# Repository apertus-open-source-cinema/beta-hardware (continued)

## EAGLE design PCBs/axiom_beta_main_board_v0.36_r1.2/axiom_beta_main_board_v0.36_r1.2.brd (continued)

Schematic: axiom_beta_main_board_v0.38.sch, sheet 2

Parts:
ZED1: µZ-FCI-NOHOLES-R; µZ-NOHOLES-R

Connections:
BANK13_00_N: ZED1.89 (_N); also elsewhere on the board
BANK13_00_P: ZED1.87 (_P); also elsewhere on the board
BANK13_01_N: ZED1.90 (_N); also elsewhere on the board
BANK13_01_P: ZED1.88 (_P); also elsewhere on the board
BANK13_02_N: ZED1.93 (_N); also elsewhere on the board
BANK13_02_P: ZED1.91 (_P); also elsewhere on the board
BANK13_03_N: ZED1.94 (_N); also elsewhere on the board
BANK13_03_P: ZED1.92 (_P); also elsewhere on the board
BANK13_04_N: ZED1.195 (_N); also elsewhere on the board
BANK13_04_P: ZED1.193 (_P); also elsewhere on the board
BANK13_05_N: ZED1.196 (_N); also elsewhere on the board
BANK13_05_P: ZED1.194 (_P); also elsewhere on the board
BANK13_06_N: ZED1.199 (_N); also elsewhere on the board
BANK13_06_P: ZED1.197 (_P); also elsewhere on the board
JX1_00_N: ZED1.13 (_N); also elsewhere on the board
JX1_00_P: ZED1.11 (_P); also elsewhere on the board
JX1_01_N: ZED1.14 (_N); also elsewhere on the board
JX1_01_P: ZED1.12 (_P); also elsewhere on the board
JX1_02_N: ZED1.19 (_N); also elsewhere on the board
JX1_02_P: ZED1.17 (_P); also elsewhere on the board
JX1_03_N: ZED1.20 (_N); also elsewhere on the board
JX1_03_P: ZED1.18 (_P); also elsewhere on the board
JX1_04_N: ZED1.25 (_N); also elsewhere on the board
JX1_04_P: ZED1.23 (_P); also elsewhere on the board
JX1_05_N: ZED1.26 (_N); also elsewhere on the board
JX1_05_P: ZED1.24 (_P); also elsewhere on the board
JX1_06_N: ZED1.31 (_N); also elsewhere on the board
JX1_06_P: ZED1.29 (_P); also elsewhere on the board
JX1_07_N: ZED1.32 (_N); also elsewhere on the board
JX1_07_P: ZED1.30 (_P); also elsewhere on the board
JX1_08_N: ZED1.37 (_N); also elsewhere on the board
JX1_08_P: ZED1.35 (_P); also elsewhere on the board
JX1_09_N: ZED1.38 (_N); also elsewhere on the board
JX1_09_P: ZED1.36 (_P); also elsewhere on the board
JX1_10_N: ZED1.43 (_N); also elsewhere on the board
JX1_10_P: ZED1.41 (_P); also elsewhere on the board
JX1_11_N: ZED1.44 (_N); also elsewhere on the board
JX1_11_P: ZED1.42 (_P); also elsewhere on the board
JX1_12_N: ZED1.49 (_N); also elsewhere on the board
JX1_12_P: ZED1.47 (_P); also elsewhere on the board
JX1_13_N: ZED1.50 (_N); also elsewhere on the board
JX1_13_P: ZED1.48 (_P); also elsewhere on the board
JX1_14_N: ZED1.55 (_N); also elsewhere on the board
JX1_14_P: ZED1.53 (_P); also elsewhere on the board
JX1_15_N: ZED1.56 (_N); also elsewhere on the board
JX1_15_P: ZED1.54 (_P); also elsewhere on the board
JX1_16_N: ZED1.63 (_N); also elsewhere on the board
JX1_16_P: ZED1.61 (_P); also elsewhere on the board
JX1_17_N: ZED1.64 (_N); also elsewhere on the board
JX1_17_P: ZED1.62 (_P); also elsewhere on the board
JX1_18_N: ZED1.69 (_N); also elsewhere on the board
JX1_18_P: ZED1.67 (_P); also elsewhere on the board
JX1_19_N: ZED1.70 (_N); also elsewhere on the board
JX1_19_P: ZED1.68 (_P); also elsewhere on the board
JX1_20_N: ZED1.75 (_N); also elsewhere on the board
JX1_20_P: ZED1.73 (_P); also elsewhere on the board
JX1_21_N: ZED1.76 (_N); also elsewhere on the board
JX1_21_P: ZED1.74 (_P); also elsewhere on the board
JX1_22_N: ZED1.83 (_N); also elsewhere on the board
JX1_22_P: ZED1.81 (_P); also elsewhere on the board
JX1_23_N: ZED1.84 (_N); also elsewhere on the board
JX1_23_P: ZED1.82 (_P); also elsewhere on the board
JX2_00_N: ZED1.119 (_N); also elsewhere on the board
JX2_00_P: ZED1.117 (_P); also elsewhere on the board
JX2_01_N: ZED1.120 (_N); also elsewhere on the board
JX2_01_P: ZED1.118 (_P); also elsewhere on the board
JX2_02_N: ZED1.125 (_N); also elsewhere on the board
JX2_02_P: ZED1.123 (_P); also elsewhere on the board
JX2_03_N: ZED1.126 (_N); also elsewhere on the board
JX2_03_P: ZED1.124 (_P); also elsewhere on the board
JX2_04_N: ZED1.131 (_N); also elsewhere on the board
JX2_04_P: ZED1.129 (_P); also elsewhere on the board
JX2_05_N: ZED1.132 (_N); also elsewhere on the board
JX2_05_P: ZED1.130 (_P); also elsewhere on the board
JX2_06_N: ZED1.137 (_N); also elsewhere on the board
JX2_06_P: ZED1.135 (_P); also elsewhere on the board
JX2_07_N: ZED1.138 (_N); also elsewhere on the board
JX2_07_P: ZED1.136 (_P); also elsewhere on the board
JX2_08_N: ZED1.143 (_N); also elsewhere on the board
JX2_08_P: ZED1.141 (_P); also elsewhere on the board
JX2_09_N: ZED1.144 (_N); also elsewhere on the board
JX2_09_P: ZED1.142 (_P); also elsewhere on the board
JX2_10_N: ZED1.149 (_N); also elsewhere on the board
JX2_10_P: ZED1.147 (_P); also elsewhere on the board
JX2_11_N: ZED1.150 (_N); also elsewhere on the board
JX2_11_P: ZED1.148 (_P); also elsewhere on the board
JX2_12_N: ZED1.155 (_N); also elsewhere on the board
JX2_12_P: ZED1.153 (_P); also elsewhere on the board
JX2_13_N: ZED1.156 (_N); also elsewhere on the board
JX2_13_P: ZED1.154 (_P); also elsewhere on the board
JX2_14_N: ZED1.163 (_N); also elsewhere on the board
JX2_14_P: ZED1.161 (_P); also elsewhere on the board
JX2_15_N: ZED1.164 (_N); also elsewhere on the board
JX2_15_P: ZED1.162 (_P); also elsewhere on the board
JX2_16_N: ZED1.169 (_N); also elsewhere on the board
JX2_16_P: ZED1.167 (_P); also elsewhere on the board
JX2_17_N: ZED1.170 (_N); also elsewhere on the board
JX2_17_P: ZED1.168 (_P); also elsewhere on the board
JX2_18_N: ZED1.175 (_N); also elsewhere on the board
JX2_18_P: ZED1.173 (_P); also elsewhere on the board
JX2_19_N: ZED1.176 (_N); also elsewhere on the board
JX2_19_P: ZED1.174 (_P); also elsewhere on the board
JX2_20_N: ZED1.183 (_N); also elsewhere on the board
JX2_20_P: ZED1.181 (_P); also elsewhere on the board
JX2_21_N: ZED1.184 (_N); also elsewhere on the board
JX2_21_P: ZED1.182 (_P); also elsewhere on the board
JX2_22_N: ZED1.189 (_N); also elsewhere on the board
JX2_22_P: ZED1.187 (_P); also elsewhere on the board
JX2_23_N: ZED1.190 (_N); also elsewhere on the board
JX2_23_P: ZED1.188 (_P); also elsewhere on the board

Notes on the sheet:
AXIOM Beta Main Board
Copyright (C) 2014-2020 H.Poetzl Licensed under CERN OHL v.1.2
ZYNQ LVDS Interface

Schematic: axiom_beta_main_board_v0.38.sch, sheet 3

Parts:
X-EAST: FX10-100/10S; FX10A-100S/10
X-WEST: FX10-100/10S; FX10A-100S/10

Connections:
!E_RESET!: X-EAST.19; also elsewhere on the board
!W_RESET!: X-WEST.19; also elsewhere on the board
E_EN: X-EAST.14; also elsewhere on the board
E_I2C_EN: X-EAST.13; also elsewhere on the board
E_I2C_V: X-EAST.11; also elsewhere on the board
E_SCK: X-EAST.12; also elsewhere on the board
E_SCL: X-EAST.15; also elsewhere on the board
E_SDA: X-EAST.17; also elsewhere on the board
E_SDI: X-EAST.16; also elsewhere on the board
E_SDO: X-EAST.18; also elsewhere on the board
E_SPI_V: X-EAST.21; also elsewhere on the board
E_VE_CV: X-EAST.90; also elsewhere on the board
E_VE_OV: X-EAST.93; also elsewhere on the board
E_VE_UV: X-EAST.91; also elsewhere on the board
GND: X-EAST.5, X-EAST.20, X-EAST.23, X-EAST.26, X-EAST.29, X-EAST.31, X-EAST.32, X-EAST.37, X-EAST.38, X-EAST.43, X-EAST.44, X-EAST.49, X-EAST.50, X-EAST.51, X-EAST.52, X-EAST.57, X-EAST.58, X-EAST.63, X-EAST.64, X-EAST.69, X-EAST.70, X-EAST.71, X-EAST.76, X-EAST.77, X-EAST.82, X-EAST.G1, X-EAST.G2, X-EAST.G3, X-EAST.G4, X-EAST.G5, X-EAST.G6, X-EAST.G7, X-EAST.G8, X-EAST.G9, X-EAST.G10, X-WEST.5, X-WEST.20, X-WEST.23, X-WEST.26, X-WEST.29, X-WEST.31, X-WEST.32, X-WEST.37, X-WEST.38, X-WEST.43, X-WEST.44, X-WEST.49, X-WEST.50, X-WEST.51, X-WEST.52, X-WEST.57, X-WEST.58, X-WEST.63, X-WEST.64, X-WEST.69, X-WEST.70, X-WEST.71, X-WEST.76, X-WEST.77, X-WEST.82, X-WEST.G1, X-WEST.G2, X-WEST.G3, X-WEST.G4, X-WEST.G5, X-WEST.G6, X-WEST.G7, X-WEST.G8, X-WEST.G9, X-WEST.G10; also elsewhere on the board
JTAG_V: X-WEST.21; also elsewhere on the board
JX1_00_N: X-EAST.27; also elsewhere on the board
JX1_00_P: X-EAST.25; also elsewhere on the board
JX1_02_N: X-EAST.24; also elsewhere on the board
JX1_02_P: X-EAST.22; also elsewhere on the board
JX1_04_N: X-EAST.30; also elsewhere on the board
JX1_04_P: X-EAST.28; also elsewhere on the board
JX1_06_N: X-EAST.36; also elsewhere on the board
JX1_06_P: X-EAST.34; also elsewhere on the board
JX1_07_N: X-EAST.35; also elsewhere on the board
JX1_07_P: X-EAST.33; also elsewhere on the board
JX1_08_N: X-EAST.42; also elsewhere on the board
JX1_08_P: X-EAST.40; also elsewhere on the board
JX1_09_N: X-EAST.41; also elsewhere on the board
JX1_09_P: X-EAST.39; also elsewhere on the board
JX1_10_N: X-EAST.48; also elsewhere on the board
JX1_10_P: X-EAST.46; also elsewhere on the board
JX1_11_N: X-EAST.47; also elsewhere on the board
JX1_11_P: X-EAST.45; also elsewhere on the board
JX1_12_N: X-WEST.56; also elsewhere on the board
JX1_12_P: X-WEST.54; also elsewhere on the board
JX1_13_N: X-WEST.55; also elsewhere on the board
JX1_13_P: X-WEST.53; also elsewhere on the board
JX1_14_N: X-WEST.62; also elsewhere on the board
JX1_14_P: X-WEST.60; also elsewhere on the board
JX1_15_N: X-WEST.61; also elsewhere on the board
JX1_15_P: X-WEST.59; also elsewhere on the board
JX1_16_N: X-WEST.68; also elsewhere on the board
JX1_16_P: X-WEST.66; also elsewhere on the board
JX1_17_N: X-WEST.67; also elsewhere on the board
JX1_17_P: X-WEST.65; also elsewhere on the board
JX1_18_N: X-WEST.74; also elsewhere on the board
JX1_18_P: X-WEST.72; also elsewhere on the board
JX1_20_N: X-WEST.80; also elsewhere on the board
JX1_20_P: X-WEST.78; also elsewhere on the board
JX1_22_N: X-WEST.75; also elsewhere on the board
JX1_22_P: X-WEST.73; also elsewhere on the board
JX2_01_N: X-EAST.73; also elsewhere on the board
JX2_01_P: X-EAST.75; also elsewhere on the board
JX2_03_N: X-EAST.78; also elsewhere on the board
JX2_03_P: X-EAST.80; also elsewhere on the board
JX2_05_N: X-EAST.72; also elsewhere on the board
JX2_05_P: X-EAST.74; also elsewhere on the board
JX2_06_N: X-EAST.65; also elsewhere on the board
JX2_06_P: X-EAST.67; also elsewhere on the board
JX2_07_N: X-EAST.66; also elsewhere on the board
JX2_07_P: X-EAST.68; also elsewhere on the board
JX2_08_N: X-EAST.59; also elsewhere on the board
JX2_08_P: X-EAST.61; also elsewhere on the board
JX2_09_N: X-EAST.60; also elsewhere on the board
JX2_09_P: X-EAST.62; also elsewhere on the board
JX2_10_N: X-EAST.53; also elsewhere on the board
JX2_10_P: X-EAST.55; also elsewhere on the board
JX2_11_N: X-EAST.54; also elsewhere on the board
JX2_11_P: X-EAST.56; also elsewhere on the board
JX2_12_N: X-WEST.45; also elsewhere on the board
JX2_12_P: X-WEST.47; also elsewhere on the board
JX2_13_N: X-WEST.46; also elsewhere on the board
JX2_13_P: X-WEST.48; also elsewhere on the board
JX2_14_N: X-WEST.39; also elsewhere on the board
JX2_14_P: X-WEST.41; also elsewhere on the board
JX2_15_N: X-WEST.40; also elsewhere on the board
JX2_15_P: X-WEST.42; also elsewhere on the board
JX2_16_N: X-WEST.33; also elsewhere on the board
JX2_16_P: X-WEST.35; also elsewhere on the board
JX2_17_N: X-WEST.34; also elsewhere on the board
JX2_17_P: X-WEST.36; also elsewhere on the board
JX2_19_N: X-WEST.28; also elsewhere on the board
JX2_19_P: X-WEST.30; also elsewhere on the board
JX2_21_N: X-WEST.22; also elsewhere on the board
JX2_21_P: X-WEST.24; also elsewhere on the board
JX2_23_N: X-WEST.25; also elsewhere on the board
JX2_23_P: X-WEST.27; also elsewhere on the board
N_CHK_EN: X-WEST.94
N_CHK_V: X-WEST.92; also elsewhere on the board
N_I2C_EN: X-EAST.7; also elsewhere on the board
N_I2C_V: X-EAST.9; also elsewhere on the board
N_SCK: X-EAST.2; also elsewhere on the board
N_SCL: X-EAST.1; also elsewhere on the board
N_SDA: X-EAST.3; also elsewhere on the board
N_SDI: X-EAST.6; also elsewhere on the board
N_SDO: X-EAST.4; also elsewhere on the board
N_SPI_EN: X-EAST.8; also elsewhere on the board
N_SPI_V: X-EAST.10; also elsewhere on the board
N_VE_CV: X-WEST.96; also elsewhere on the board
N_VE_OV: X-WEST.95; also elsewhere on the board
N_VE_RS: X-WEST.88; also elsewhere on the board
N_VE_UV: X-WEST.85; also elsewhere on the board
N_VN_CV: X-WEST.98; also elsewhere on the board
N_VN_OV: X-WEST.97; also elsewhere on the board
N_VN_RS: X-WEST.86; also elsewhere on the board
N_VN_UV: X-WEST.87; also elsewhere on the board
N_VW_CV: X-WEST.100; also elsewhere on the board
N_VW_OV: X-WEST.99; also elsewhere on the board
N_VW_RS: X-WEST.84; also elsewhere on the board
N_VW_UV: X-WEST.89; also elsewhere on the board
RES1: X-WEST.79
RES2: X-WEST.81
RES3: X-WEST.83
RES4: X-EAST.79
RES5: X-EAST.81
RES6: X-EAST.83
S_CHK_EN: X-EAST.94
S_CHK_V: X-EAST.92; also elsewhere on the board
S_I2C_EN: X-WEST.7; also elsewhere on the board
S_I2C_V: X-WEST.9; also elsewhere on the board
S_SCK: X-WEST.2; also elsewhere on the board
S_SCL: X-WEST.1; also elsewhere on the board
S_SDA: X-WEST.3; also elsewhere on the board
S_SDI: X-WEST.6; also elsewhere on the board
S_SDO: X-WEST.4; also elsewhere on the board
S_SPI_EN: X-WEST.8; also elsewhere on the board
S_SPI_V: X-WEST.10; also elsewhere on the board
S_VE_CV: X-EAST.100; also elsewhere on the board
S_VE_OV: X-EAST.99; also elsewhere on the board
S_VE_RS: X-EAST.84; also elsewhere on the board
S_VE_UV: X-EAST.89; also elsewhere on the board
S_VS_CV: X-EAST.98; also elsewhere on the board
S_VS_OV: X-EAST.97; also elsewhere on the board
S_VS_RS: X-EAST.86; also elsewhere on the board
S_VS_UV: X-EAST.87; also elsewhere on the board
S_VW_CV: X-EAST.96; also elsewhere on the board
S_VW_OV: X-EAST.95; also elsewhere on the board
S_VW_RS: X-EAST.88; also elsewhere on the board
S_VW_UV: X-EAST.85; also elsewhere on the board
TCK: X-WEST.12; also elsewhere on the board
TDI: X-WEST.16; also elsewhere on the board
TDO: X-WEST.18; also elsewhere on the board
TMS: X-WEST.14; also elsewhere on the board
W_I2C_EN: X-WEST.13; also elsewhere on the board
W_I2C_V: X-WEST.11; also elsewhere on the board
W_SCL: X-WEST.15; also elsewhere on the board
W_SDA: X-WEST.17; also elsewhere on the board
W_VW_CV: X-WEST.90; also elsewhere on the board
W_VW_OV: X-WEST.93; also elsewhere on the board
W_VW_UV: X-WEST.91; also elsewhere on the board

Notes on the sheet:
AXIOM Beta Main Board
Copyright (C) 2014-2020 H.Poetzl Licensed under CERN OHL v.1.2
Interface Board Connection

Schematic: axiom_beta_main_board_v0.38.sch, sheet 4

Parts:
C1, C1', C3, C3', C5, C5', C7, C7': C0805-A; 0805-A
C2, C2', C4, C4', C6, C6', C8, C8': C0603-A; 0603-A
PAD1, PAD2, PAD3, PAD4, PAD5, PAD6, PAD7, PAD8, PAD9, PAD10, PAD11, PAD12, PAD13, PAD14, PAD15, PAD16: PINPAD1.27MM; 1.2/0.6
PB-NW: DF12(XX)-20DP-0.5V
PB-SE: DF12(XX)-20DP-0.5V
PCIE-NORTH: PCIE-36-AXIOM-NOPEG; PCIE-36-NOPEG
PCIE-SOUTH: PCIE-36-AXIOM-NOPEG; PCIE-36-NOPEG
PWR-NE: PINHD-2X02_2.54; 2X02
PWR-NW: PINHD-2X02_2.54; 2X02
PWR-SE: PINHD-2X02_2.54; 2X02
PWR-SW: PINHD-2X02_2.54; 2X02
R1, R2, R3, R4, R5, R6: 4k7; 0402-B
U1: PCA9540BDP; SOP65P490X300-8N

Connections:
A_!RST: PB-NW.2; also elsewhere on the board
A_SCL: PB-NW.1; also elsewhere on the board
A_SDA: PB-NW.3; also elsewhere on the board
BANK13_00_N: PCIE-NORTH.B17 (LVDS_5B); also elsewhere on the board
BANK13_00_P: PCIE-NORTH.B16 (LVDS_5A); also elsewhere on the board
BANK13_02_N: PCIE-NORTH.A16 (LVDS_4A); also elsewhere on the board
BANK13_02_P: PCIE-NORTH.A17 (LVDS_4B); also elsewhere on the board
BANK13_03_N: PCIE-NORTH.A14 (LVDS_3B); also elsewhere on the board
BANK13_03_P: PCIE-NORTH.A13 (LVDS_3A); also elsewhere on the board
BANK13_04_N: PCIE-SOUTH.A6 (LVDS_1B); also elsewhere on the board
BANK13_04_P: PCIE-SOUTH.A5 (LVDS_1A); also elsewhere on the board
BANK13_05_N: PCIE-SOUTH.A3 (LVDS_0B); also elsewhere on the board
BANK13_05_P: PCIE-SOUTH.A2 (LVDS_0A); also elsewhere on the board
BANK13_06_N: PCIE-SOUTH.A8 (LVDS_2A); also elsewhere on the board
BANK13_06_P: PCIE-SOUTH.A9 (LVDS_2B); also elsewhere on the board
B_!RST: PB-SE.2; also elsewhere on the board
B_SCL: PB-SE.1; also elsewhere on the board
B_SDA: PB-SE.3; also elsewhere on the board
CSO_NE_V: C3.1, C3'.1, C4.1, C4'.1, PAD2.1; also elsewhere on the board
CSO_NW_V: C1.1, C1'.1, C2.1, C2'.1, PAD15.1, PWR-NW.1
CSO_SE_V: C7.1, C7'.1, C8.1, C8'.1, PAD7.1, PWR-SE.1
CSO_SW_V: C5.1, C5'.1, C6.1, C6'.1, PAD10.1; also elsewhere on the board
C_CK_E: PAD5.1; also elsewhere on the board
C_CK_W: PAD13.1; also elsewhere on the board
C_EN_E: PAD3.1; also elsewhere on the board
C_EN_W: PAD11.1; also elsewhere on the board
C_SI_E: PAD4.1; also elsewhere on the board
C_SI_W: PAD12.1; also elsewhere on the board
C_SO_E: PAD6.1; also elsewhere on the board
C_SO_W: PAD14.1; also elsewhere on the board
E_I2C_V: PWR-NE.1; also elsewhere on the board
E_SPI_V: PWR-NE.3; also elsewhere on the board
E_VE_CV: PB-SE.19; also elsewhere on the board
E_VE_OV: PB-SE.10; also elsewhere on the board
E_VE_UV: PB-SE.12; also elsewhere on the board
GND: C1.2, C1'.2, C2.2, C2'.2, C3.2, C3'.2, C4.2, C4'.2, C5.2, C5'.2, C6.2, C6'.2, C7.2, C7'.2, C8.2, C8'.2, PAD1.1, PAD8.1, PAD9.1, PAD16.1, PB-NW.5, PB-SE.5, PCIE-NORTH.A1 (GND), PCIE-NORTH.A4 (GND), PCIE-NORTH.A7 (GND), PCIE-NORTH.A10 (GND), PCIE-NORTH.A12 (GND), PCIE-NORTH.A15 (GND), PCIE-NORTH.A18 (GND), PCIE-NORTH.B15 (GND), PCIE-NORTH.B18 (GND), PCIE-SOUTH.A1 (GND), PCIE-SOUTH.A4 (GND), PCIE-SOUTH.A7 (GND), PCIE-SOUTH.A10 (GND), PCIE-SOUTH.A12 (GND), PCIE-SOUTH.A15 (GND), PCIE-SOUTH.A18 (GND), PCIE-SOUTH.B15 (GND), PCIE-SOUTH.B18 (GND), U1.6 (VSS); also elsewhere on the board
JTAG_V: PWR-SW.3; also elsewhere on the board
JX1_19_N: PCIE-NORTH.A3 (LVDS_0B); also elsewhere on the board
JX1_19_P: PCIE-NORTH.A2 (LVDS_0A); also elsewhere on the board
JX1_21_N: PCIE-NORTH.A6 (LVDS_1B); also elsewhere on the board
JX1_21_P: PCIE-NORTH.A5 (LVDS_1A); also elsewhere on the board
JX1_23_N: PCIE-NORTH.A9 (LVDS_2B); also elsewhere on the board
JX1_23_P: PCIE-NORTH.A8 (LVDS_2A); also elsewhere on the board
JX2_18_N: PCIE-SOUTH.B17 (LVDS_5B); also elsewhere on the board
JX2_18_P: PCIE-SOUTH.B16 (LVDS_5A); also elsewhere on the board
JX2_20_N: PCIE-SOUTH.A17 (LVDS_4B); also elsewhere on the board
JX2_20_P: PCIE-SOUTH.A16 (LVDS_4A); also elsewhere on the board
JX2_22_N: PCIE-SOUTH.A13 (LVDS_3A); also elsewhere on the board
JX2_22_P: PCIE-SOUTH.A14 (LVDS_3B); also elsewhere on the board
N_CHK_V: PB-NW.14; also elsewhere on the board
N_I2C_V: PWR-NE.4; also elsewhere on the board
N_SPI_V: PWR-NE.2; also elsewhere on the board
N_VE_CV: PB-NW.17; also elsewhere on the board
N_VE_OV: PB-NW.8; also elsewhere on the board
N_VE_RS: PB-NW.7; also elsewhere on the board
N_VE_UV: PB-NW.20; also elsewhere on the board
N_VN_CV: PB-NW.15; also elsewhere on the board
N_VN_OV: PB-NW.6; also elsewhere on the board
N_VN_RS: PB-NW.11; also elsewhere on the board
N_VN_UV: PB-NW.18; also elsewhere on the board
N_VW_CV: PB-NW.13; also elsewhere on the board
N_VW_OV: PB-NW.4; also elsewhere on the board
N_VW_RS: PB-NW.9; also elsewhere on the board
N_VW_UV: PB-NW.16; also elsewhere on the board
PCIE_I2C_V: PCIE-NORTH.B3 (V_I2C), PCIE-SOUTH.B3 (V_I2C), R3.1, R4.1, R5.1, R6.1, U1.3 (VDD); also elsewhere on the board
PCIE_N_5V: PCIE-NORTH.B12 (5V); also elsewhere on the board
PCIE_N_IO0: PCIE-NORTH.B4 (IO0); also elsewhere on the board
PCIE_N_IO1: PCIE-NORTH.B5 (IO1); also elsewhere on the board
PCIE_N_IO2: PCIE-NORTH.B6 (IO2); also elsewhere on the board
PCIE_N_IO3: PCIE-NORTH.B7 (IO3); also elsewhere on the board
PCIE_N_IO4: PCIE-NORTH.B8 (IO4); also elsewhere on the board
PCIE_N_IO5: PCIE-NORTH.B9 (IO5); also elsewhere on the board
PCIE_N_IO6: PCIE-NORTH.B10 (IO6); also elsewhere on the board
PCIE_N_IO7: PCIE-NORTH.B11 (IO7); also elsewhere on the board
PCIE_N_SCL: PCIE-NORTH.B2 (SCL), R4.2, U1.5 (SC0)
PCIE_N_SDA: PCIE-NORTH.B1 (SDA), R3.2, U1.4 (SD0)
PCIE_N_V: PCIE-NORTH.B13 (VCC); also elsewhere on the board
PCIE_N_VCCIO: PCIE-NORTH.B14 (VCCIO); also elsewhere on the board
PCIE_SCL: R2.2, U1.1 (SCL); also elsewhere on the board
PCIE_SDA: R1.2, U1.2 (SDA); also elsewhere on the board
PCIE_S_5V: PCIE-SOUTH.B12 (5V); also elsewhere on the board
PCIE_S_IO0: PCIE-SOUTH.B4 (IO0); also elsewhere on the board
PCIE_S_IO1: PCIE-SOUTH.B5 (IO1); also elsewhere on the board
PCIE_S_IO2: PCIE-SOUTH.B6 (IO2); also elsewhere on the board
PCIE_S_IO3: PCIE-SOUTH.B7 (IO3); also elsewhere on the board
PCIE_S_IO4: PCIE-SOUTH.B8 (IO4); also elsewhere on the board
PCIE_S_IO5: PCIE-SOUTH.B9 (IO5); also elsewhere on the board
PCIE_S_IO6: PCIE-SOUTH.B10 (IO6); also elsewhere on the board
PCIE_S_IO7: PCIE-SOUTH.B11 (IO7); also elsewhere on the board
PCIE_S_SCL: PCIE-SOUTH.B2 (SCL), R6.2, U1.8 (SC1)
PCIE_S_SDA: PCIE-SOUTH.B1 (SDA), R5.2, U1.7 (SD1)
PCIE_S_V: PCIE-SOUTH.B13 (VCC); also elsewhere on the board
PCIE_S_VCCIO: PCIE-SOUTH.B14 (VCCIO); also elsewhere on the board
RFAB_E_V: PWR-SE.3; also elsewhere on the board
RFAB_W_V: PWR-NW.3; also elsewhere on the board
SH_NW_V: PWR-NW.4; also elsewhere on the board
SH_NW_VIO: PWR-NW.2, R1.1, R2.1; also elsewhere on the board
SH_SE_V: PWR-SE.4; also elsewhere on the board
SH_SE_VIO: PWR-SE.2; also elsewhere on the board
S_CHK_V: PB-SE.14; also elsewhere on the board
S_I2C_V: PWR-SW.4; also elsewhere on the board
S_SPI_V: PWR-SW.2; also elsewhere on the board
S_VE_CV: PB-SE.13; also elsewhere on the board
S_VE_OV: PB-SE.4; also elsewhere on the board
S_VE_RS: PB-SE.9; also elsewhere on the board
S_VE_UV: PB-SE.16; also elsewhere on the board
S_VS_CV: PB-SE.15; also elsewhere on the board
S_VS_OV: PB-SE.6; also elsewhere on the board
S_VS_RS: PB-SE.11; also elsewhere on the board
S_VS_UV: PB-SE.18; also elsewhere on the board
S_VW_CV: PB-SE.17; also elsewhere on the board
S_VW_OV: PB-SE.8; also elsewhere on the board
S_VW_RS: PB-SE.7; also elsewhere on the board
S_VW_UV: PB-SE.20; also elsewhere on the board
W_I2C_V: PWR-SW.1; also elsewhere on the board
W_VW_CV: PB-NW.19; also elsewhere on the board
W_VW_OV: PB-NW.10; also elsewhere on the board
W_VW_UV: PB-NW.12; also elsewhere on the board

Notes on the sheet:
AXIOM Beta Main Board
Copyright (C) 2015-2020 H.Poetzl Licensed under CERN OHL v.1.2
PCIE, Power, Center Area

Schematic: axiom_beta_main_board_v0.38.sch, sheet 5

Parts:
C9, C10, C11, C12, C13, C41: 100n; 0402-B
C19, C20, C21, C22, C23, C24, C25, C26, C27, C28, C29: 10n; 0402-B
HDR-NW: PINHD-2X08_2.00_LPR; 62101621821
HDR-SW: PINHD-2X08_2.00_LPR; 62101621821
R7: 50R; 0402-B
R15: 100R; 0201-B
R18: 10k; 0402-B
RFW: MACHXO2-100; MACHXO2-100TQFP
U2: PIC16F1718-I/MV; QFN40P400X400X55-29N

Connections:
!SS!_W: RFW.27 (CSSPIN), U2.4 (RA5)
!W_RESET!: U2.1 (RA2); also elsewhere on the board
A_!RST: R18.2, U2.26 (RE3/!MCLR!/VPP); also elsewhere on the board
A_SCL: U2.24 (RB6/ICSPCLK); also elsewhere on the board
A_SDA: U2.25 (RB7/ICSPDAT); also elsewhere on the board
BANK13_01_N: R15.2, RFW.38 (PB11A); also elsewhere on the board
BANK13_01_P: R15.1, RFW.39 (PB11B); also elsewhere on the board
BANK13_SE_0: R7.1, RFW.88 (PT12A), U2.7 (RA6); also elsewhere on the board
C_CK_W: RFW.18 (PL8C); also elsewhere on the board
C_EN_W: RFW.14 (PL5C); also elsewhere on the board
C_SI_W: RFW.19 (PL8D); also elsewhere on the board
C_SO_W: RFW.15 (PL5D); also elsewhere on the board
DONE_W: RFW.76 (DONE), U2.20 (RB2)
GND: C9.2, C10.2, C11.2, C12.2, C13.2, C19.2, C20.2, C21.2, C22.2, C23.2, C24.2, C25.2, C26.2, C27.2, C28.2, C29.2, C41.2, HDR-SW.1, HDR-SW.2, R7.2, RFW.6 (GND), RFW.22 (GND), RFW.33 (GND), RFW.44 (GND), RFW.56 (GND), RFW.72 (GND), RFW.79 (GND), RFW.92 (GND), U2.5 (VSS), U2.16 (VSS), U2.29 (EPAD); also elsewhere on the board
INITN_W: RFW.77 (INITN), U2.18 (RB0)
JTAGENB_W: RFW.82 (JTAGENB), U2.14 (RC6)
PB22B_W: RFW.47 (PB18D), U2.23 (RB5)
PCIE_N_IO0: RFW.83 (PT15B); also elsewhere on the board
PCIE_N_IO1: RFW.78 (PT16C); also elsewhere on the board
PCIE_N_IO2: RFW.74 (PR2B); also elsewhere on the board
PCIE_N_IO3: RFW.75 (PR2A); also elsewhere on the board
PCIE_N_IO4: RFW.71 (PR3A); also elsewhere on the board
PCIE_N_IO5: RFW.70 (PR3B); also elsewhere on the board
PCIE_N_IO6: RFW.69 (PR4A); also elsewhere on the board
PCIE_N_IO7: RFW.68 (PR4B); also elsewhere on the board
PCIE_SCL: RFW.86 (SCL), U2.12 (RC4); also elsewhere on the board
PCIE_SDA: RFW.85 (SDA), U2.13 (RC5); also elsewhere on the board
PCIE_S_IO0: RFW.1 (PL2C); also elsewhere on the board
PCIE_S_IO1: RFW.2 (PL2D); also elsewhere on the board
PCIE_S_IO2: RFW.98 (PT9B); also elsewhere on the board
PCIE_S_IO3: RFW.99 (PT9A); also elsewhere on the board
PCIE_S_IO4: RFW.96 (PT10B); also elsewhere on the board
PCIE_S_IO5: RFW.97 (PT10A); also elsewhere on the board
PCIE_S_IO6: RFW.84 (PT15A); also elsewhere on the board
PCIE_S_IO7: RFW.87 (PT12B); also elsewhere on the board
PROGRAMN_W: RFW.81 (PROGRAMN), U2.15 (RC7)
RFAB_W_V: C9.1, C10.1, C19.1, C20.1, RFW.50 (VCC), RFW.100 (VCC); also elsewhere on the board
SCK_W: RFW.31 (MCLK), U2.3 (RA4)
SDI_W: RFW.49 (SI/SISPI), U2.21 (RB3)
SDO_W: RFW.32 (SO/SPISO), U2.2 (RA3)
SH_NW_IO0: HDR-NW.4, RFW.67 (PR4C)
SH_NW_IO1: HDR-NW.3, RFW.66 (PR4D)
SH_NW_IO2: HDR-NW.6, RFW.65 (PR5A)
SH_NW_IO3: HDR-NW.5, RFW.64 (PR5B)
SH_NW_IO4: HDR-NW.8, RFW.63 (PR5C)
SH_NW_IO5: HDR-NW.7, RFW.62 (PR5D)
SH_NW_IO6: HDR-NW.10, RFW.60 (PR8C)
SH_NW_IO7: HDR-NW.9, RFW.59 (PR8D)
SH_NW_IO8: HDR-NW.12, RFW.58 (PR9A)
SH_NW_IO9: HDR-NW.11, RFW.57 (PR9B)
SH_NW_V: HDR-NW.2; also elsewhere on the board
SH_NW_VIO: C11.1, C12.1, C13.1, C21.1, C22.1, C23.1, C24.1, C25.1, C26.1, C27.1, C28.1, C29.1, C41.1, HDR-NW.1, R18.1, RFW.5 (VCCIO5), RFW.11 (VCCIO4), RFW.23 (VCCIO3), RFW.26 (VCCIO2), RFW.46 (VCCIO2), RFW.55 (VCCIO1), RFW.73 (VCCIO1), RFW.80 (VCCIO0), RFW.93 (VCCIO0), U2.17 (VDD); also elsewhere on the board
SH_SW_IO0: HDR-SW.4, RFW.4 (PL3B)
SH_SW_IO1: HDR-SW.3, RFW.3 (PL3A)
SH_SW_IO2: HDR-SW.6, RFW.8 (PL3D)
SH_SW_IO3: HDR-SW.5, RFW.7 (PL3C)
SH_SW_IO4: HDR-SW.8, RFW.10 (PL4B)
SH_SW_IO5: HDR-SW.7, RFW.9 (PL4A)
SH_SW_IO6: HDR-SW.10, RFW.12 (PL5A)
SH_SW_IO7: HDR-SW.9, RFW.13 (PL5B)
SH_SW_IO8: HDR-SW.12, RFW.16 (PL8A)
SH_SW_IO9: HDR-SW.11, RFW.17 (PL8B)
SN_W: RFW.48 (SN), U2.22 (RB4)
S_I2C_EN: U2.28 (RA1); also elsewhere on the board
S_SCK: RFW.28 (PB4D); also elsewhere on the board
S_SCL: RFW.34 (PB9A); also elsewhere on the board
S_SDA: RFW.35 (PB9B); also elsewhere on the board
S_SDI: RFW.30 (PB6B); also elsewhere on the board
S_SDO: RFW.29 (PB6A); also elsewhere on the board
S_SPI_EN: RFW.45 (PB18C); also elsewhere on the board
TCK: RFW.43 (PB18B); also elsewhere on the board
TCK_W: RFW.91 (TCK), U2.10 (RC2)
TDI: RFW.41 (PB15B); also elsewhere on the board
TDI_W: RFW.94 (TDI), U2.9 (RC1)
TDO: RFW.40 (PB15A); also elsewhere on the board
TDO_W: RFW.95 (TDO), U2.8 (RC0)
TMS: RFW.42 (PB18A); also elsewhere on the board
TMS_W: RFW.90 (TMS), U2.11 (RC3)
W_I2C_EN: U2.27 (RA0); also elsewhere on the board
W_SCL: RFW.36 (PB11C); also elsewhere on the board
W_SDA: RFW.37 (PB11D); also elsewhere on the board
XX1_N: HDR-NW.13, RFW.52 (PR10C)
XX1_P: HDR-NW.15, RFW.51 (PR10D)
XX2_N: HDR-NW.14, RFW.54 (PR9C)
XX2_P: HDR-NW.16, RFW.53 (PR9D)
XX3_N: HDR-SW.16, RFW.25 (PL10D)
XX3_P: HDR-SW.14, RFW.24 (PL10C)
XX4_N: HDR-SW.15, RFW.21 (PL9B)
XX4_P: HDR-SW.13, RFW.20 (PL9A)

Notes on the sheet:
AXIOM Beta Main Board
Copyright (C) 2015-2020 H.Poetzl Licensed under CERN OHL v.1.2
Interface Fabric West

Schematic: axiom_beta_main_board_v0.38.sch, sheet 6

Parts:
C14, C15, C16, C17, C18, C42: 100n; 0402-B
C30, C31, C32, C33, C34, C35, C36, C37, C38, C39, C40: 10n; 0402-B
HDR-NE: PINHD-2X08_2.00_LPR; 62101621821
HDR-SE: PINHD-2X08_2.00_LPR; 62101621821
R8: 50R; 0402-B
R16, R17: 100R; 0201-B
R19: 10k; 0402-B
RFE: MACHXO2-100; MACHXO2-100TQFP
U3: PIC16F1718-I/MV; QFN40P400X400X55-29N

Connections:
!E_RESET!: U3.1 (RA2); also elsewhere on the board
!SS!_E: RFE.27 (CSSPIN), U3.4 (RA5)
B_!RST: R19.2, U3.26 (RE3/!MCLR!/VPP); also elsewhere on the board
B_SCL: U3.24 (RB6/ICSPCLK); also elsewhere on the board
B_SDA: U3.25 (RB7/ICSPDAT); also elsewhere on the board
C_CK_E: RFE.18 (PL8C); also elsewhere on the board
C_EN_E: RFE.14 (PL5C); also elsewhere on the board
C_SI_E: RFE.19 (PL8D); also elsewhere on the board
C_SO_E: RFE.15 (PL5D); also elsewhere on the board
DONE_E: RFE.76 (DONE), U3.20 (RB2)
E_EN: RFE.20 (PL9A); also elsewhere on the board
E_I2C_EN: U3.27 (RA0); also elsewhere on the board
E_IO0: RFE.99 (PT9A)
E_IO1: RFE.98 (PT9B)
E_IO2: RFE.97 (PT10A)
E_IO3: RFE.96 (PT10B)
E_IO5: RFE.87 (PT12B)
E_IO6: RFE.84 (PT15A)
E_IO7: RFE.83 (PT15B)
E_SCK: RFE.21 (PL9B); also elsewhere on the board
E_SCL: RFE.36 (PB11C); also elsewhere on the board
E_SDA: RFE.37 (PB11D); also elsewhere on the board
E_SDI: RFE.24 (PL10C); also elsewhere on the board
E_SDO: RFE.25 (PL10D); also elsewhere on the board
GND: C14.2, C15.2, C16.2, C17.2, C18.2, C30.2, C31.2, C32.2, C33.2, C34.2, C35.2, C36.2, C37.2, C38.2, C39.2, C40.2, C42.2, HDR-NE.1, HDR-NE.2, R8.2, RFE.6 (GND), RFE.22 (GND), RFE.33 (GND), RFE.44 (GND), RFE.56 (GND), RFE.72 (GND), RFE.79 (GND), RFE.92 (GND), U3.5 (VSS), U3.16 (VSS), U3.29 (EPAD); also elsewhere on the board
INITN_E: RFE.77 (INITN), U3.18 (RB0)
IO_SCL: RFE.86 (SCL), U3.12 (RC4)
IO_SDA: RFE.85 (SDA), U3.13 (RC5)
JTAGENB_E: RFE.82 (JTAGENB), U3.14 (RC6)
JX1_01_N: HDR-NE.13; also elsewhere on the board
JX1_01_P: HDR-NE.15; also elsewhere on the board
JX1_03_N: HDR-NE.14; also elsewhere on the board
JX1_03_P: HDR-NE.16; also elsewhere on the board
JX1_05_N: R16.2, RFE.35 (PB9B); also elsewhere on the board
JX1_05_P: R16.1, RFE.34 (PB9A); also elsewhere on the board
JX1_SE_0: R8.1, RFE.88 (PT12A), U3.7 (RA6); also elsewhere on the board
JX2_00_N: HDR-SE.14; also elsewhere on the board
JX2_00_P: HDR-SE.16; also elsewhere on the board
JX2_02_N: HDR-SE.13; also elsewhere on the board
JX2_02_P: HDR-SE.15; also elsewhere on the board
JX2_04_N: R17.1, RFE.38 (PB11A); also elsewhere on the board
JX2_04_P: R17.2, RFE.39 (PB11B); also elsewhere on the board
N_I2C_EN: U3.28 (RA1); also elsewhere on the board
N_IO0: RFE.1 (PL2C); also elsewhere on the board
N_IO1: RFE.2 (PL2D)
N_SCK: RFE.42 (PB18A); also elsewhere on the board
N_SCL: RFE.28 (PB4D); also elsewhere on the board
N_SDA: RFE.30 (PB6B); also elsewhere on the board
N_SDI: RFE.29 (PB6A); also elsewhere on the board
N_SDO: RFE.43 (PB18B); also elsewhere on the board
N_SPI_EN: RFE.45 (PB18C); also elsewhere on the board
PB22B_E: RFE.47 (PB18D), U3.23 (RB5)
PROGRAMN_E: RFE.81 (PROGRAMN), U3.15 (RC7)
RFAB_E_V: C14.1, C15.1, C30.1, C31.1, RFE.50 (VCC), RFE.100 (VCC); also elsewhere on the board
SCK_E: RFE.31 (MCLK), U3.3 (RA4)
SDI_E: RFE.49 (SI/SISPI), U3.21 (RB3)
SDO_E: RFE.32 (SO/SPISO), U3.2 (RA3)
SH_NE_IO0: HDR-NE.4, RFE.4 (PL3B)
SH_NE_IO1: HDR-NE.3, RFE.3 (PL3A)
SH_NE_IO2: HDR-NE.6, RFE.8 (PL3D)
SH_NE_IO3: HDR-NE.5, RFE.7 (PL3C)
SH_NE_IO4: HDR-NE.8, RFE.10 (PL4B)
SH_NE_IO5: HDR-NE.7, RFE.9 (PL4A)
SH_NE_IO6: HDR-NE.10, RFE.12 (PL5A)
SH_NE_IO7: HDR-NE.9, RFE.13 (PL5B)
SH_NE_IO8: HDR-NE.12, RFE.16 (PL8A)
SH_NE_IO9: HDR-NE.11, RFE.17 (PL8B)
SH_SE_IO0: HDR-SE.4, RFE.67 (PR4C)
SH_SE_IO1: HDR-SE.3, RFE.66 (PR4D)
SH_SE_IO2: HDR-SE.6, RFE.65 (PR5A)
SH_SE_IO3: HDR-SE.5, RFE.64 (PR5B)
SH_SE_IO4: HDR-SE.8, RFE.63 (PR5C)
SH_SE_IO5: HDR-SE.7, RFE.62 (PR5D)
SH_SE_IO6: HDR-SE.10, RFE.60 (PR8C)
SH_SE_IO7: HDR-SE.9, RFE.59 (PR8D)
SH_SE_IO8: HDR-SE.12, RFE.58 (PR9A)
SH_SE_IO9: HDR-SE.11, RFE.57 (PR9B)
SH_SE_V: HDR-SE.2; also elsewhere on the board
SH_SE_VIO: C16.1, C17.1, C18.1, C32.1, C33.1, C34.1, C35.1, C36.1, C37.1, C38.1, C39.1, C40.1, C42.1, HDR-SE.1, R19.1, RFE.5 (VCCIO5), RFE.11 (VCCIO4), RFE.23 (VCCIO3), RFE.26 (VCCIO2), RFE.46 (VCCIO2), RFE.55 (VCCIO1), RFE.73 (VCCIO1), RFE.80 (VCCIO0), RFE.93 (VCCIO0), U3.17 (VDD); also elsewhere on the board
SN_E: RFE.48 (SN), U3.22 (RB4)
S_IO0: RFE.75 (PR2A); also elsewhere on the board
S_IO1: RFE.74 (PR2B)
S_IO2: RFE.71 (PR3A)
S_IO3: RFE.70 (PR3B)
S_IO4: RFE.69 (PR4A)
S_IO5: RFE.68 (PR4B)
S_IO6: RFE.54 (PR9C)
S_IO7: RFE.53 (PR9D)
S_IO8: RFE.52 (PR10C)
S_IO9: RFE.51 (PR10D)
TCK_E: RFE.91 (TCK), U3.10 (RC2)
TDI_E: RFE.94 (TDI), U3.9 (RC1)
TDO_E: RFE.95 (TDO), U3.8 (RC0)
TMS_E: RFE.90 (TMS), U3.11 (RC3)

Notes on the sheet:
AXIOM Beta Main Board
Copyright (C) 2015-2020 H.Poetzl Licensed under CERN OHL v.1.2
Interface Fabric East

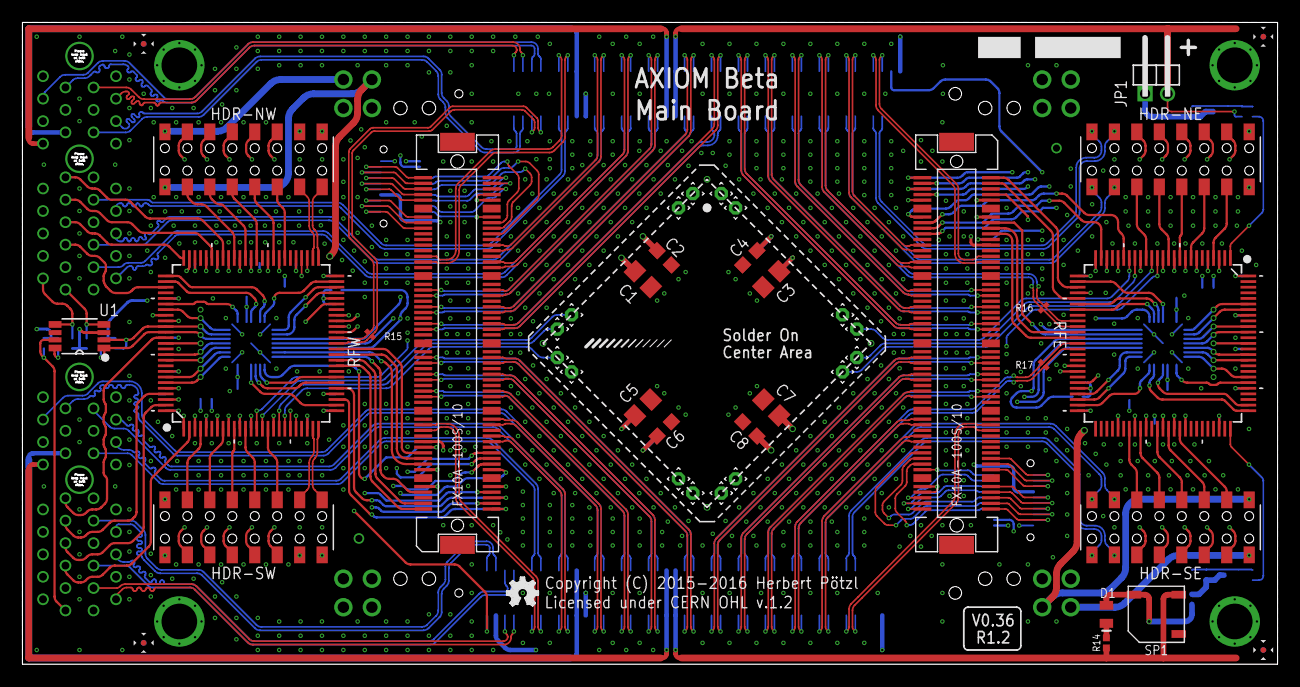
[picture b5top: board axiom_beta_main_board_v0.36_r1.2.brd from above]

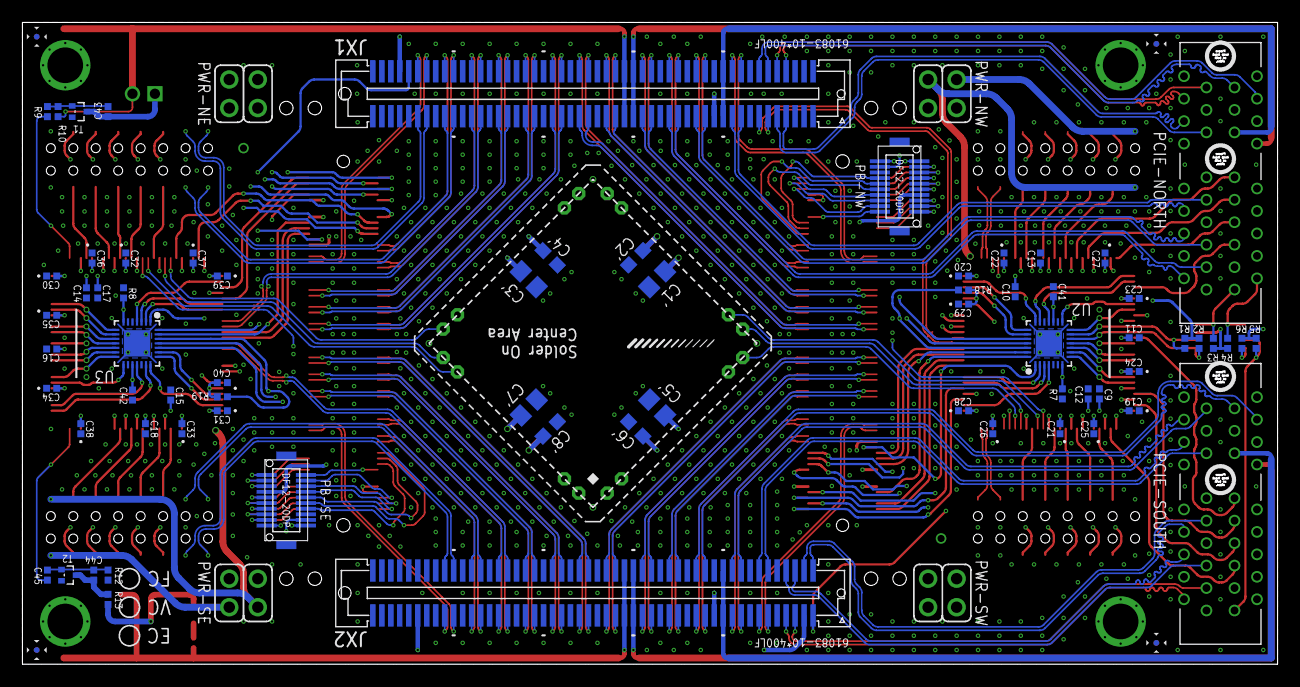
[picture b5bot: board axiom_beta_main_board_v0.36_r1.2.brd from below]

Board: 4 copper layers, 111.8 x 57.1 mm, 113 parts (72 on the bottom side), 324 nets.

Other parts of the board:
LOGO1: OSHW_LOGO_FILLX0100-NT; OSHW_FILLX100_NOTEXT

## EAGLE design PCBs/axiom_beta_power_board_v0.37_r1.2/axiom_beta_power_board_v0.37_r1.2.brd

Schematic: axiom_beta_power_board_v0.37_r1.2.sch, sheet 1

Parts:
FID5, FID6, FID7, FID8: FIDUCIAL; FID_ARROW
JX1B, JX2B: BERGSTAK-61083; 61083
VP+: TPTP16SQ; TP16SQ
VP-: TPTP16SQ; TP16SQ
ZED: µZ-FCI-CONONLY; µZ-CONONLY

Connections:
AB_SCL: ZED.113 (_0); also elsewhere on the board
AB_SDA: ZED.114 (_1); also elsewhere on the board
BANK13_SE_0: ZED.200 (_0); also elsewhere on the board
DXP_0_N: ZED.100 (_N)
DXP_0_P: ZED.98 (_P)
GND: ZED.15 (GND), ZED.16 (GND), ZED.21 (GND), ZED.22 (GND), ZED.27 (GND), ZED.28 (GND), ZED.33 (GND), ZED.34 (GND), ZED.39 (GND), ZED.40 (GND), ZED.45 (GND), ZED.46 (GND), ZED.51 (GND), ZED.52 (GND), ZED.65 (GND), ZED.66 (GND), ZED.71 (GND), ZED.72 (GND), ZED.77 (GND), ZED.85 (GND), ZED.86 (GND), ZED.95 (GND), ZED.96 (GND), ZED.115 (GND), ZED.116 (GND), ZED.121 (GND), ZED.122 (GND), ZED.127 (GND), ZED.128 (GND), ZED.133 (GND), ZED.134 (GND), ZED.139 (GND), ZED.140 (GND), ZED.145 (GND), ZED.146 (GND), ZED.151 (GND), ZED.152 (GND), ZED.165 (GND), ZED.166 (GND), ZED.171 (GND), ZED.172 (GND), ZED.177 (GND), ZED.185 (GND), ZED.186 (GND), ZED.191 (GND), ZED.192 (GND); also elsewhere on the board
SE_0: ZED.9 (_0); also elsewhere on the board
SE_1: ZED.10 (_1); also elsewhere on the board
VBAT: ZED.7 (FPGA_VBAT)
VCCO_13: ZED.198 (VCCO_13); also elsewhere on the board
VCCO_34: ZED.78 (VCCO_34), ZED.79 (VCCO_34), ZED.80 (VCCO_34); also elsewhere on the board
VCCO_35: ZED.178 (VCCO_35), ZED.179 (VCCO_35), ZED.180 (VCCO_35); also elsewhere on the board
VP_0_N: VP-.TP, ZED.99 (_N)
VP_0_P: VP+.TP, ZED.97 (_P)
ZED_5V': ZED.57 (VIN_HDR), ZED.58 (VIN_HDR), ZED.59 (VIN_HDR), ZED.60 (VIN_HDR), ZED.112 (VIN_HDR), ZED.157 (VIN_HDR), ZED.158 (VIN_HDR), ZED.159 (VIN_HDR), ZED.160 (VIN_HDR); also elsewhere on the board

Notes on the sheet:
AXIOM Beta Power Board
Copyright (C) 2014-2020 H.Poetzl Licensed under CERN OHL v.1.2
MicroZed Power [Bottom]
Smart Power
RFE CLK
RFW CLK
